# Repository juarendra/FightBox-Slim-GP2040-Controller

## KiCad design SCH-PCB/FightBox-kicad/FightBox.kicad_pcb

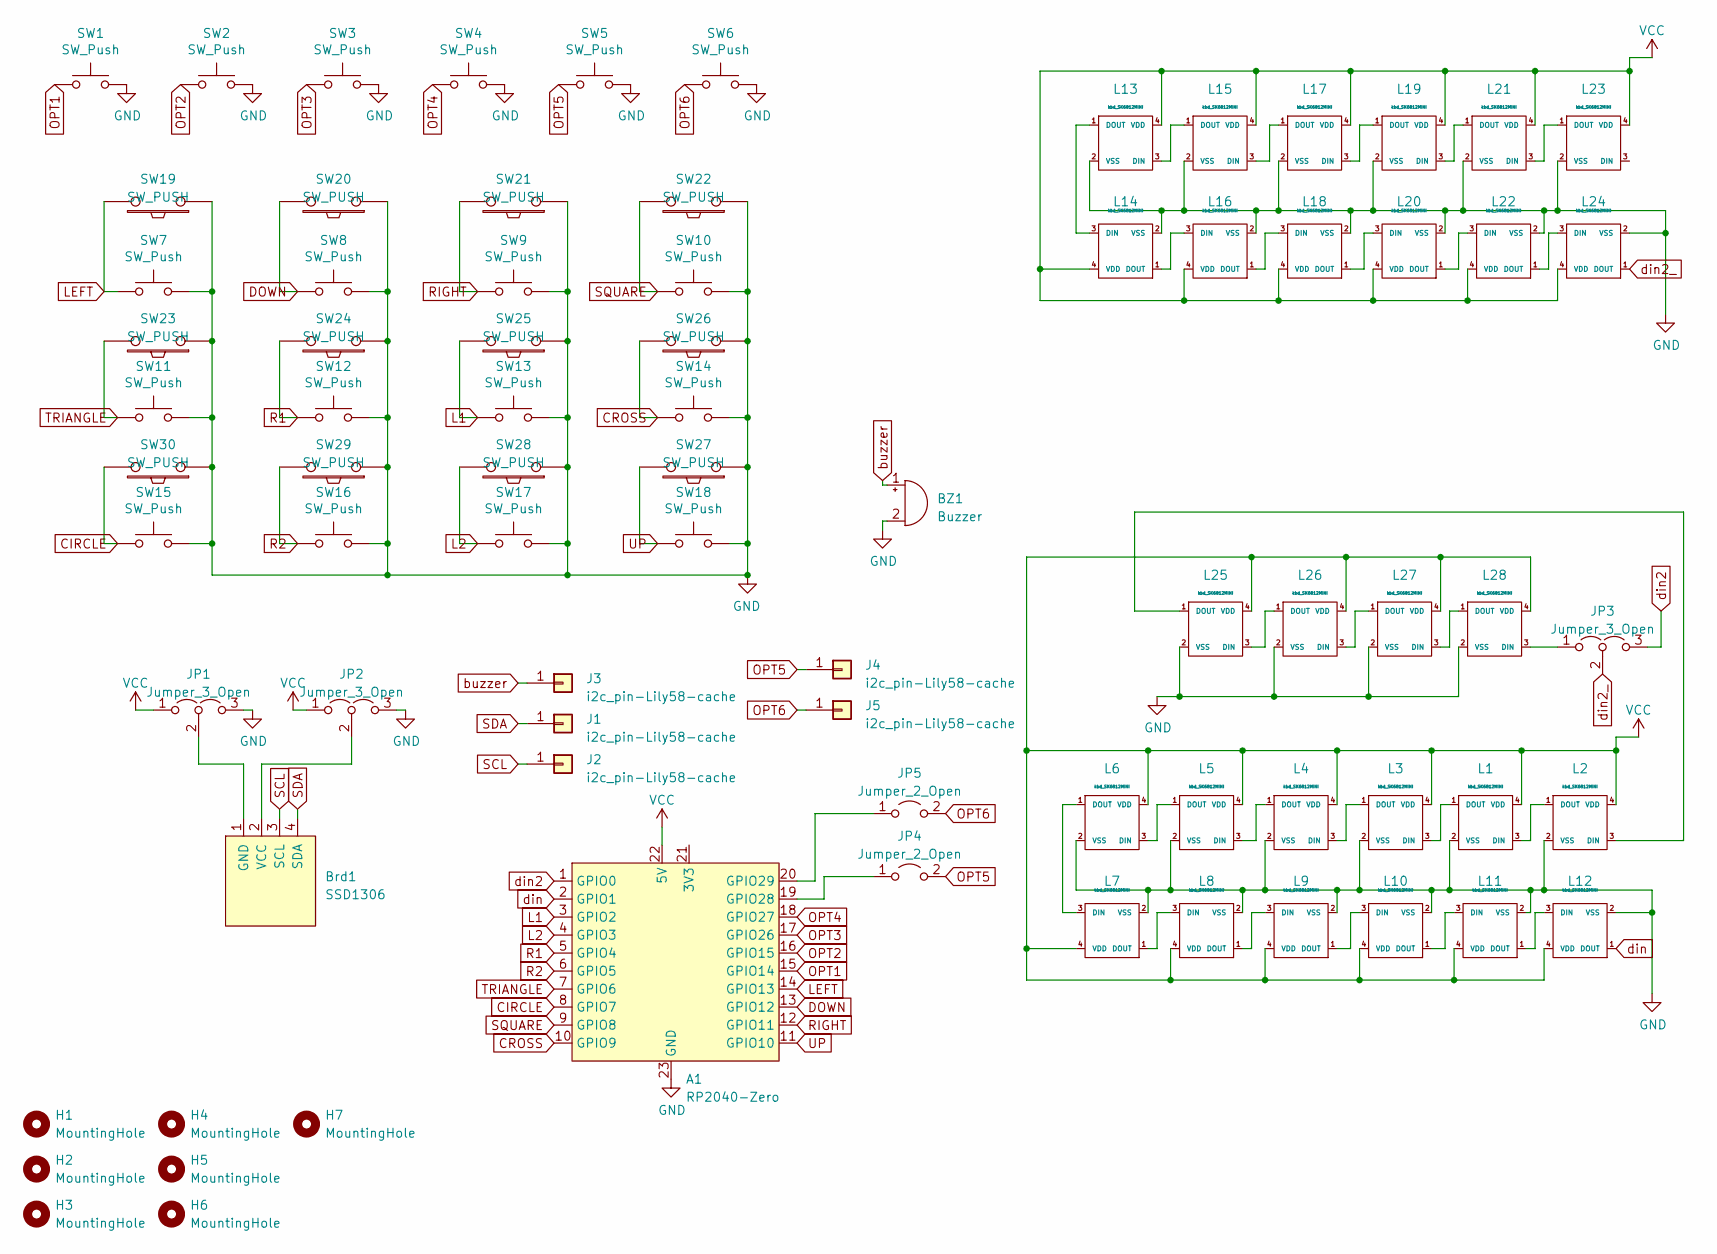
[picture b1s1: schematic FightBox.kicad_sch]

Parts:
A1: RP2040-Zero
BZ1: Buzzer; Buzzer_Murata_PKLCS1212E
Brd1: SSD1306; 128x64OLED
H1, H2, H3, H4, H5, H6, H7: MountingHole; MountingHole_6.4mm_M6
J1, J2, J3, J4, J5: i2c_pin-Lily58-cache; 1pin_conn
JP1, JP2, JP3: Jumper_3_Open; SolderJumper-3_P1.3mm_Open_RoundedPad1.0x1.5mm
JP4, JP5: Jumper_2_Open; SolderJumper-2_P1.3mm_Open_RoundedPad1.0x1.5mm
L1, L2, L3, L4, L5, L6, L7, L8, L9, L10, L11, L12, L13, L14, L15, L16, L17, L18, L19, L20, L21, L22, L23, L24, L25, L26, L27, L28: kbd_SK6812MINI; SK6812MINI_rev
SW1, SW2, SW3, SW4, SW5, SW6: SW_Push; SW_PUSH_6mm_H5mm
SW7, SW8, SW9, SW10, SW11, SW12, SW13, SW14, SW15, SW16, SW17, SW18: SW_Push; Kailh_socket_PG1350
SW19, SW20, SW21, SW22, SW23, SW24, SW25, SW26, SW27, SW28, SW29, SW30: SW_PUSH; Kailh_socket_MX

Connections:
CIRCLE: A1.8 (GPIO7), SW15.1, SW30.2
CROSS: A1.10 (GPIO9), SW14.1, SW26.2
DOWN: A1.13 (GPIO12), SW8.1, SW20.2
GND: A1.23 (GND), BZ1.2 (+), JP1.3 (B), JP2.3 (B), L1.2 (VSS), L2.2 (VSS), L3.2 (VSS), L4.2 (VSS), L5.2 (VSS), L6.2 (VSS), L7.2 (VSS), L8.2 (VSS), L9.2 (VSS), L10.2 (VSS), L11.2 (VSS), L12.2 (VSS), L13.2 (VSS), L14.2 (VSS), L15.2 (VSS), L16.2 (VSS), L17.2 (VSS), L18.2 (VSS), L19.2 (VSS), L20.2 (VSS), L21.2 (VSS), L22.2 (VSS), L23.2 (VSS), L24.2 (VSS), L25.2 (VSS), L26.2 (VSS), L27.2 (VSS), L28.2 (VSS), SW1.2, SW2.2, SW3.2, SW4.2, SW5.2, SW6.2, SW7.2, SW8.2, SW9.2, SW10.2, SW11.2, SW12.2, SW13.2, SW14.2, SW15.2, SW16.2, SW17.2, SW18.2, SW19.1, SW20.1, SW21.1, SW22.1, SW23.1, SW24.1, SW25.1, SW26.1, SW27.1, SW28.1, SW29.1, SW30.1
L1: A1.3 (GPIO2), SW13.1, SW25.2
L2: A1.4 (GPIO3), SW17.1, SW28.2
LEFT: A1.14 (GPIO13), SW7.1, SW19.2
unnamed: A1.19 (GPIO28), JP4.1 (A)
unnamed: A1.20 (GPIO29), JP5.1 (A)
unnamed: Brd1.1 (GND), JP1.2 (C)
unnamed: Brd1.2 (VCC), JP2.2 (C)
unnamed: JP3.1 (A), L28.3 (DIN)
unnamed: L1.3 (DIN), L2.1 (DOUT)
unnamed: L1.1 (DOUT), L3.3 (DIN)
unnamed: L2.3 (DIN), L25.1 (DOUT)
unnamed: L3.1 (DOUT), L4.3 (DIN)
unnamed: L4.1 (DOUT), L5.3 (DIN)
unnamed: L5.1 (DOUT), L6.3 (DIN)
unnamed: L6.1 (DOUT), L7.3 (DIN)
unnamed: L7.1 (DOUT), L8.3 (DIN)
unnamed: L8.1 (DOUT), L9.3 (DIN)
unnamed: L9.1 (DOUT), L10.3 (DIN)
unnamed: L10.1 (DOUT), L11.3 (DIN)
unnamed: L11.1 (DOUT), L12.3 (DIN)
unnamed: L13.3 (DIN), L15.1 (DOUT)
unnamed: L13.1 (DOUT), L14.3 (DIN)
unnamed: L14.1 (DOUT), L16.3 (DIN)
unnamed: L15.3 (DIN), L17.1 (DOUT)
unnamed: L16.1 (DOUT), L18.3 (DIN)
unnamed: L17.3 (DIN), L19.1 (DOUT)
unnamed: L18.1 (DOUT), L20.3 (DIN)
unnamed: L19.3 (DIN), L21.1 (DOUT)
unnamed: L20.1 (DOUT), L22.3 (DIN)
unnamed: L21.3 (DIN), L23.1 (DOUT)
unnamed: L22.1 (DOUT), L24.3 (DIN)
unnamed: L25.3 (DIN), L26.1 (DOUT)
unnamed: L26.3 (DIN), L27.1 (DOUT)
unnamed: L27.3 (DIN), L28.1 (DOUT)
OPT1: A1.15 (GPIO14), SW1.1
OPT2: A1.16 (GPIO15), SW2.1
OPT3: A1.17 (GPIO26), SW3.1
OPT4: A1.18 (GPIO27), SW4.1
OPT5: J4.1, JP4.2 (B), SW5.1
OPT6: J5.1, JP5.2 (B), SW6.1
R1: A1.5 (GPIO4), SW12.1, SW24.2
R2: A1.6 (GPIO5), SW16.1, SW29.2
RIGHT: A1.12 (GPIO11), SW9.1, SW21.2
SCL: Brd1.3 (SCL), J2.1
SDA: Brd1.4 (SDA), J1.1
SQUARE: A1.9 (GPIO8), SW10.1, SW22.2
TRIANGLE: A1.7 (GPIO6), SW11.1, SW23.2
UP: A1.11 (GPIO10), SW18.1, SW27.2
VCC: A1.22 (5V), JP1.1 (A), JP2.1 (A), L1.4 (VDD), L2.4 (VDD), L3.4 (VDD), L4.4 (VDD), L5.4 (VDD), L6.4 (VDD), L7.4 (VDD), L8.4 (VDD), L9.4 (VDD), L10.4 (VDD), L11.4 (VDD), L12.4 (VDD), L13.4 (VDD), L14.4 (VDD), L15.4 (VDD), L16.4 (VDD), L17.4 (VDD), L18.4 (VDD), L19.4 (VDD), L20.4 (VDD), L21.4 (VDD), L22.4 (VDD), L23.4 (VDD), L24.4 (VDD), L25.4 (VDD), L26.4 (VDD), L27.4 (VDD), L28.4 (VDD)
buzzer: BZ1.1 (-), J3.1
din: A1.2 (GPIO1), L12.1 (DOUT)
din2: A1.1 (GPIO0), JP3.3 (B)
din2_: JP3.2 (C), L24.1 (DOUT)

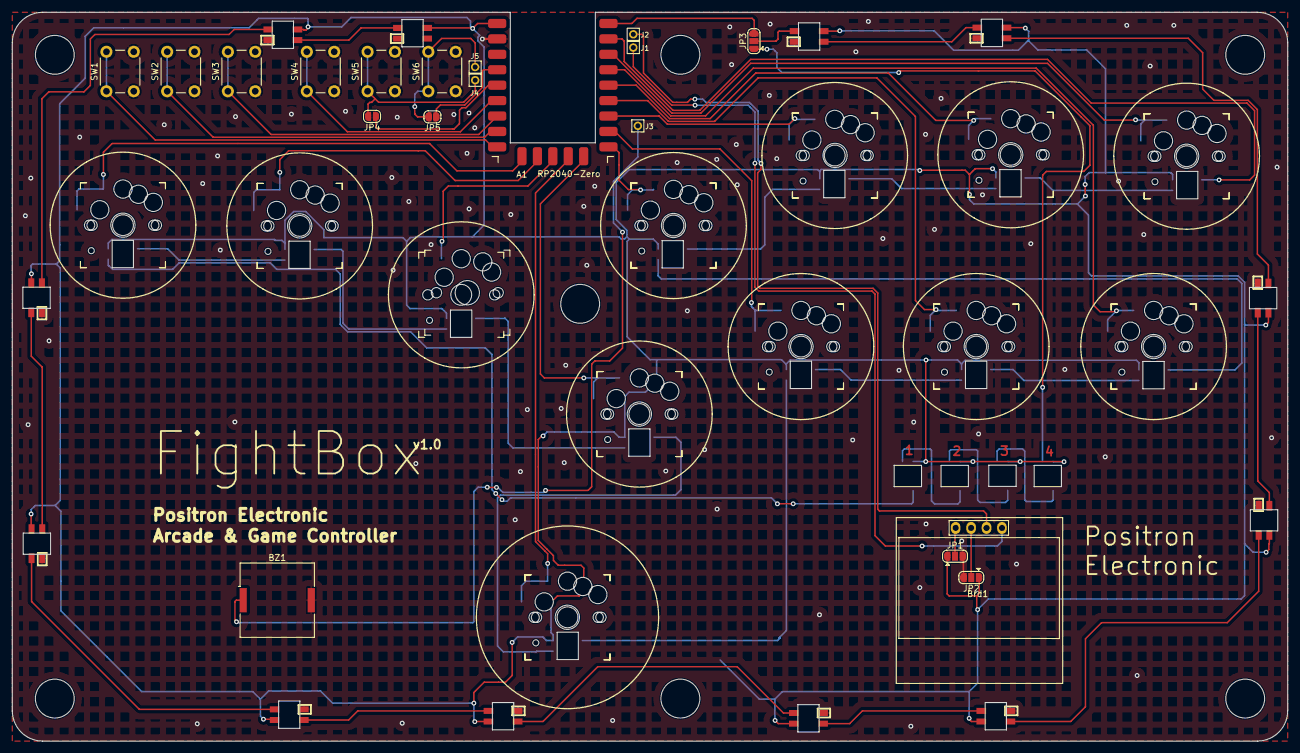
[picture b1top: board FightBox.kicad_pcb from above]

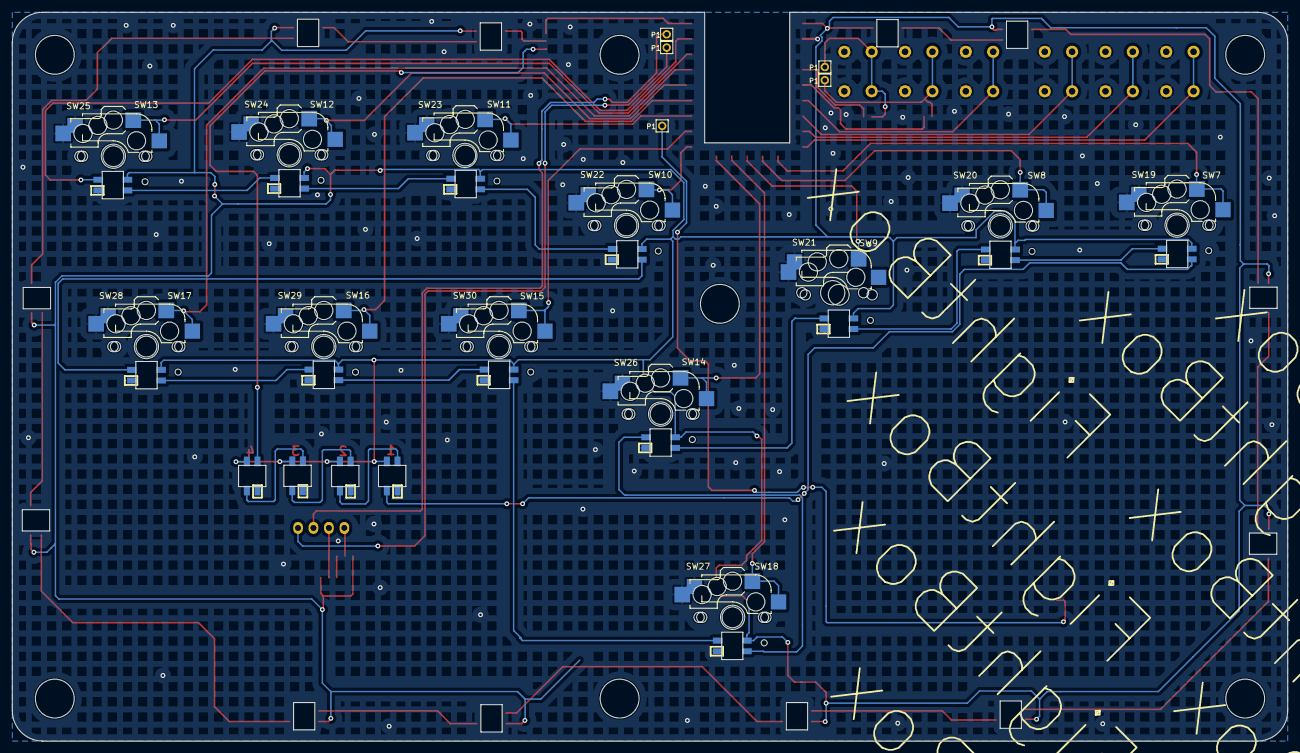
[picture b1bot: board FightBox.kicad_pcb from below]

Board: 2 copper layers, 209.9 x 119.9 mm, 78 parts (12 on the bottom side), 57 nets.

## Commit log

2024-08-05 FEAT: add 3d model, case, shematic
2024-08-05 DOC: add documentation on readme
2024-08-05 FEATL: add BOM List
2024-08-05 FEATL: add pinout document
2024-08-05 DOC: update readme
